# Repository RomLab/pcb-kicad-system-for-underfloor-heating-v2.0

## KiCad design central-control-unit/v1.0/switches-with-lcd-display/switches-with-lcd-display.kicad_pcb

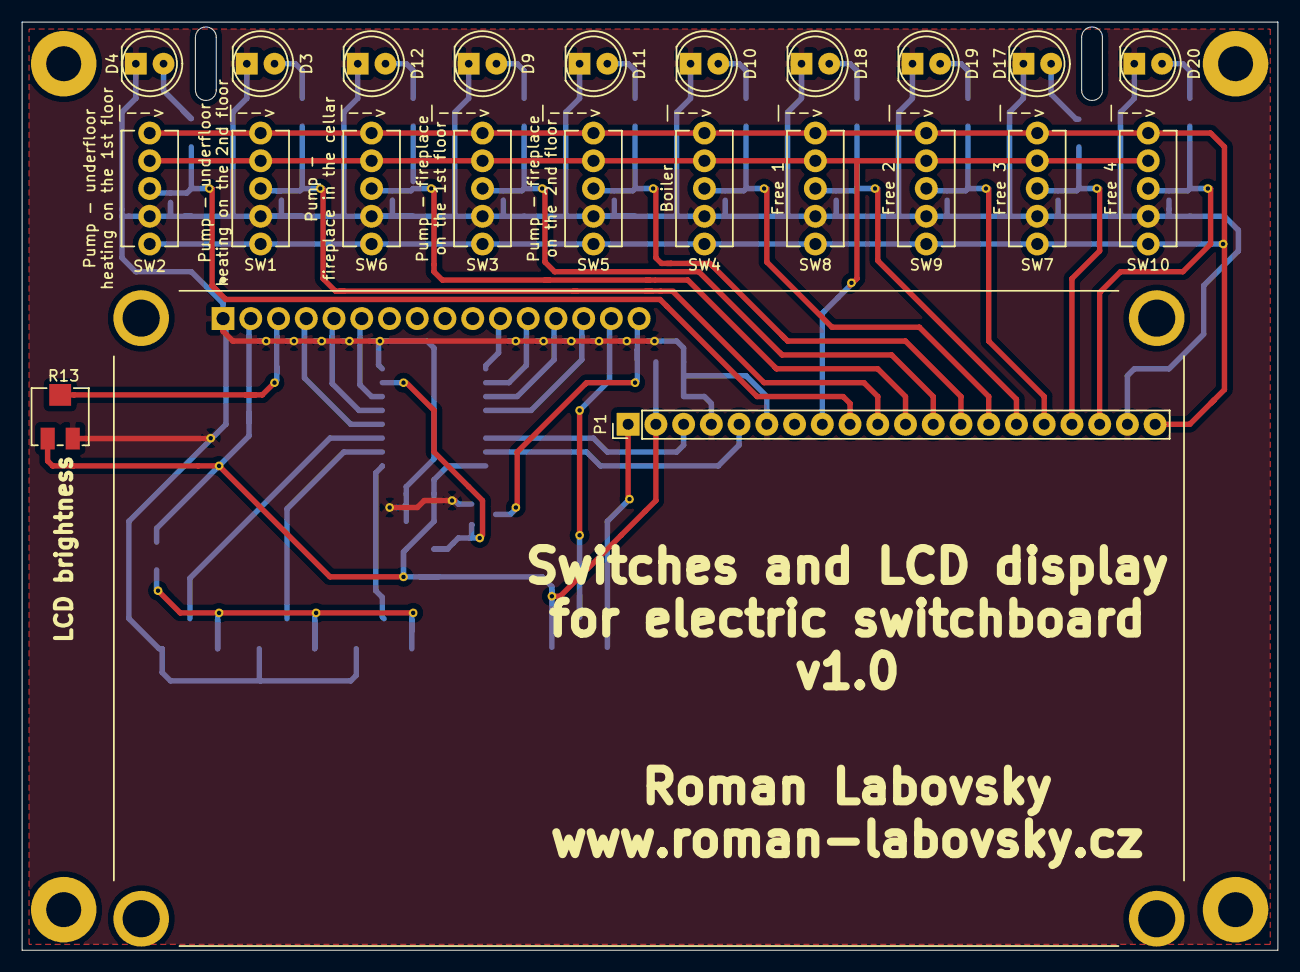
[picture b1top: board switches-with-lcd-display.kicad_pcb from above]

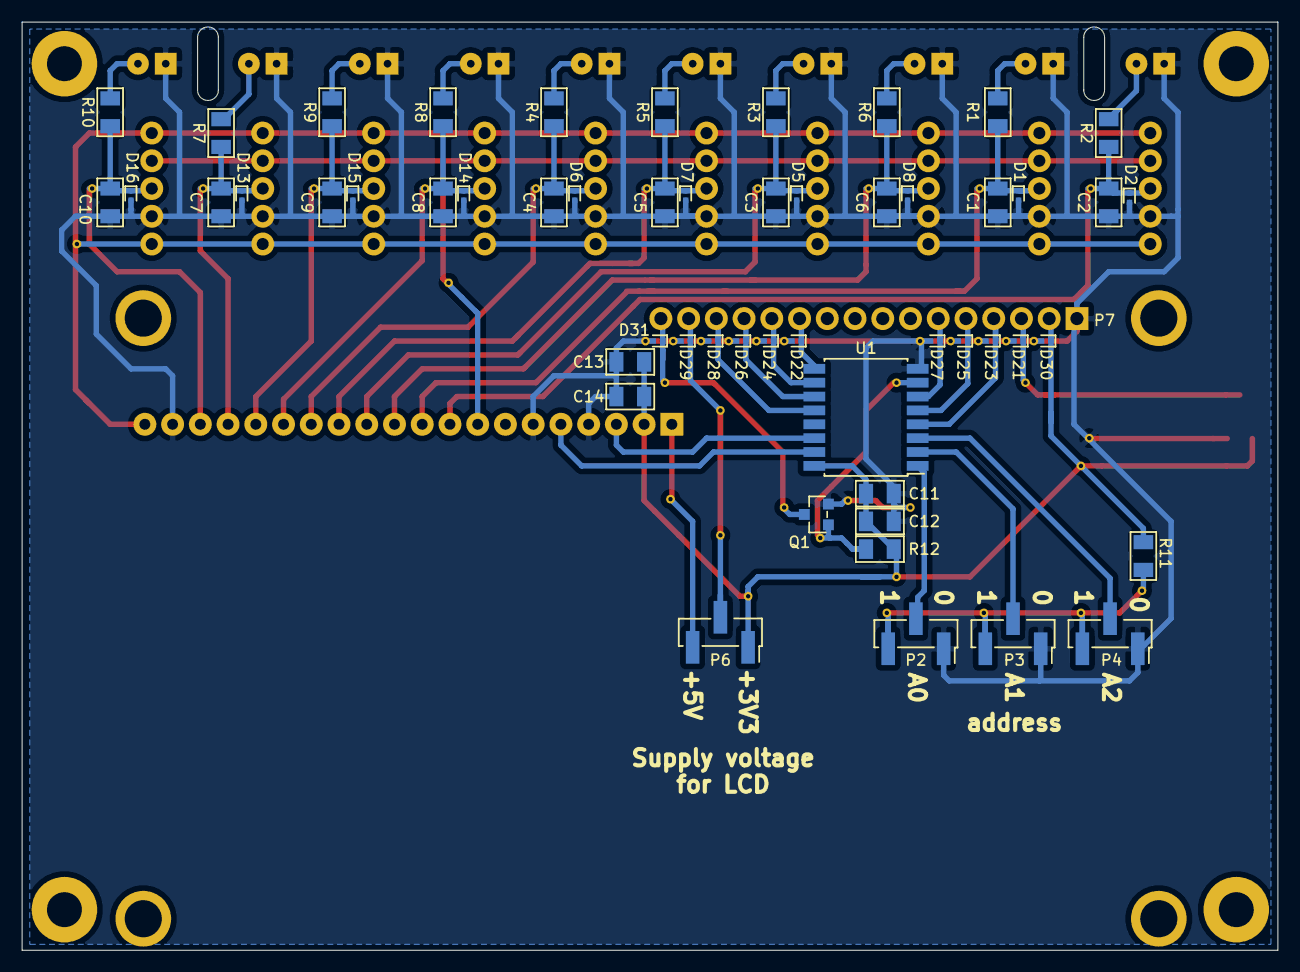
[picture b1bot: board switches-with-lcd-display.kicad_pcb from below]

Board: 2 copper layers, 115.0 x 85.0 mm, 76 parts (53 on the bottom side), 42 nets.

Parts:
C1, C2, C3, C4, C5, C6, C7, C8, C9, C10, C11, C14: 100nF; c_1206
C12, C13: 1uF; c_1206
D1, D2, D5, D6, D7, D8, D13, D14, D15, D16, D21, D22, D23, D24, D25, D26, D27, D28, D29, D30, D31: ESD9R3.3ST5G; sod_923
D3, D4, D9, D10, D11, D12, D17, D18, D19, D20: LL-504PGC1E-G5-2B; led_d5mm_2.54mm
P1: 1x20_pin_header; 1x20_pinheader_2.54mm_vertical
P2, P3, P4, P6: 1x3_pin_header; 1x3_pinheader_2.54mm_vertical
P7: 1x16_pin_header; lcd_module_2004a_20x4
Q1: PMV213SN,215; sot_23
R1, R2, R3, R4, R5, R6, R7, R8, R9, R10: 30R; r_1206
R11, R12: 10k; r_1206
R13: 10k–20k; trimmer_ts53yj
SW1, SW2, SW3, SW4, SW5, SW6, SW7, SW8, SW9, SW10: SMTS-102-2C2T
U1: PCF8574T; so_16

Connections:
/CS: D27.1, P7.6, U1.6
/DB4: D22.1, P7.11, U1.9
/DB5: D24.1, P7.12, U1.10
/DB6: D26.1, P7.13, U1.11
/DB7: D28.1, P7.14, U1.12
/I2C_SCL: P1.3, U1.14
/I2C_SDA: P1.5, U1.15
/LED_A: D29.1, P6.2, P7.15
/LED_K: D31.1, P7.16, Q1.3
/P3_LED_K: Q1.1, R12.2, U1.7
/PCF8574T_A0: P2.2, U1.1
/PCF8574T_A1: P3.2, U1.2
/PCF8574T_A2: P4.2, U1.3
/RS: D23.1, P7.4, U1.4
/RW: D25.1, P7.5, U1.5
/SWITCH_BOILER_3V3: C4.1, D6.1, P1.14, R4.1, SW4.3
/SWITCH_FREE1_3V3: C8.1, D14.1, P1.15, R8.1, SW8.3
/SWITCH_FREE2_3V3: C9.1, D15.1, P1.16, R9.1, SW9.3
/SWITCH_FREE3_3V3: C7.1, D13.1, P1.17, R7.1, SW7.3
/SWITCH_FREE4_3V3: C10.1, D16.1, P1.18, R10.1, SW10.3
/SWITCH_PUMP_FIREPLACE_CELLAR_3V3: C6.1, D8.1, P1.11, R6.1, SW6.3
/SWITCH_PUMP_FIREPLACE_FIRST_FLOOR_3V3: C3.1, D5.1, P1.12, R3.1, SW3.3
/SWITCH_PUMP_FIREPLACE_SECOND_FLOOR_3V3: C5.1, D7.1, P1.13, R5.1, SW5.3
/SWITCH_PUMP_UNDERFLOOR_HEATING_FIRST_FOOR_3V3: C2.1, D2.1, P1.9, R2.1, SW2.3
/SWITCH_PUMP_UNDERFLOOR_HEATING_SECOND_FOOR_3V3: C1.1, D1.1, P1.10, R1.1, SW1.3
/VO: D21.1, P7.3, R13.2
Earth_Protective: P1.20, SW1.1, SW1.5, SW2.1, SW2.5, SW3.1, SW3.5, SW4.1, SW4.5, SW5.1, SW5.5, SW6.1, SW6.5, SW7.1, SW7.5, SW8.1, SW8.5, SW9.1, SW9.5, SW10.1, SW10.5
GND_A: C1.2, C2.2, C3.2, C4.2, C5.2, C6.2, C7.2, C8.2, C9.2, C10.2, C11.1, C12.1, C13.1, C14.1, D1.2, D2.2, D3.1, D4.1, D5.2, D6.2, D7.2, D8.2, D9.1, D10.1, D11.1, D12.1, D13.2, D14.2, D15.2, D16.2, D17.1, D18.1, D19.1, D20.1, D21.2, D22.2, D23.2, D24.2, D25.2, D26.2, D27.2, D28.2, D29.2, D30.2, D31.2, P1.4, P1.6, P1.19, P2.1, P3.1, P4.1, P7.1, Q1.2, R13.1, SW1.4, SW2.4, SW3.4, SW4.4, SW5.4, SW6.4, SW7.4, SW8.4, SW9.4, SW10.4, U1.8
unnamed: D3.2, R1.2
unnamed: D4.2, R2.2
unnamed: D9.2, R3.2
unnamed: D10.2, R4.2
unnamed: D11.2, R5.2
unnamed: D12.2, R6.2
unnamed: D17.2, R7.2
unnamed: D18.2, R8.2
unnamed: D19.2, R9.2
unnamed: D20.2, R10.2
unnamed: P2.3, P3.3, P4.3, R11.2
OTHER_+3V3_A: C11.2, C12.2, C13.2, C14.2, D30.1, P1.2, P6.1, P7.2, R11.1, R12.1, R13.3, U1.16
OTHER_+3V3_B: P1.8, SW1.2, SW2.2, SW3.2, SW4.2, SW5.2, SW6.2, SW7.2, SW8.2, SW9.2, SW10.2
OTHER_+5V: P1.1, P6.3

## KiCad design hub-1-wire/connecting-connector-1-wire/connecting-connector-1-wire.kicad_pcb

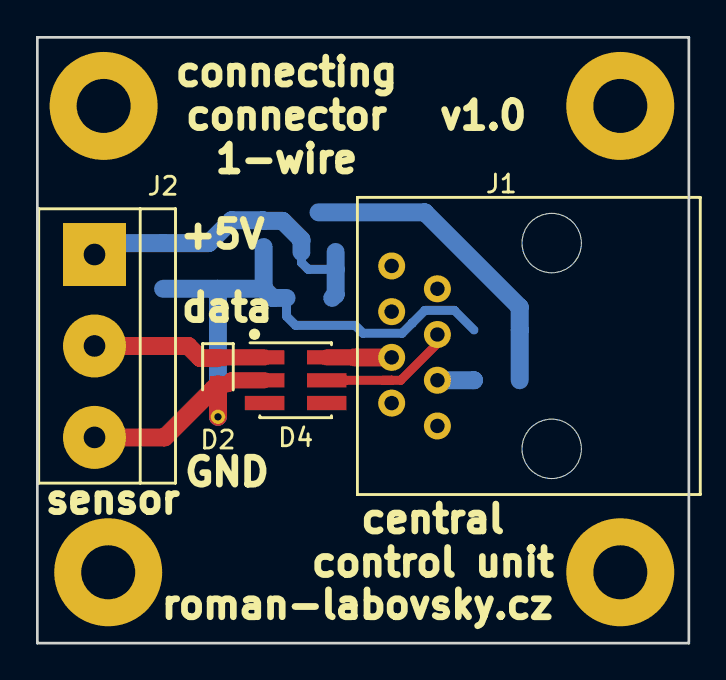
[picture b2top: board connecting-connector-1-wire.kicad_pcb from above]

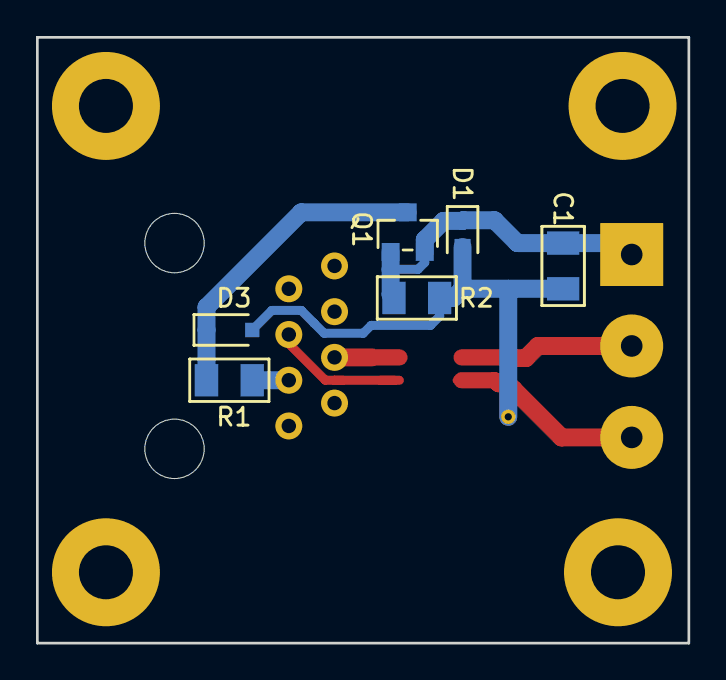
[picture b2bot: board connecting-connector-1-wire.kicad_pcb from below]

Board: 2 copper layers, 36.2 x 33.7 mm, 10 parts (6 on the bottom side), 7 nets.

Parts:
C1: 10uF; c_1206
D1, D2: UCLAMP0501H.TCT; sod_523
D3: ESD3B5V0WS; sod_323
D4: DS9503; tsoc_6
J1: 54601-908WPLF; rj45_54601-908WPLF
J2: Screw_Terminal_01x03; EBBA-03-C-SS-BU
Q1: YJL3415A; sot_23
R1: 10R/0.5W; r_1206
R2: 100k; r_1206

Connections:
/1WIRE_5V: J1.3, R1.1
/1WIRE_5V_OUT: C1.1, D1.1, J2.1, Q1.1, Q1.2, R2.2
/data: D4.6, J1.4
GND: C1.2, D1.2, D2.2, D3.2, D4.2, J2.3, R2.1
unnamed: D2.1, D4.1, J2.2
unnamed: D3.1, Q1.3, R1.2
unnamed: D4.5, J1.5

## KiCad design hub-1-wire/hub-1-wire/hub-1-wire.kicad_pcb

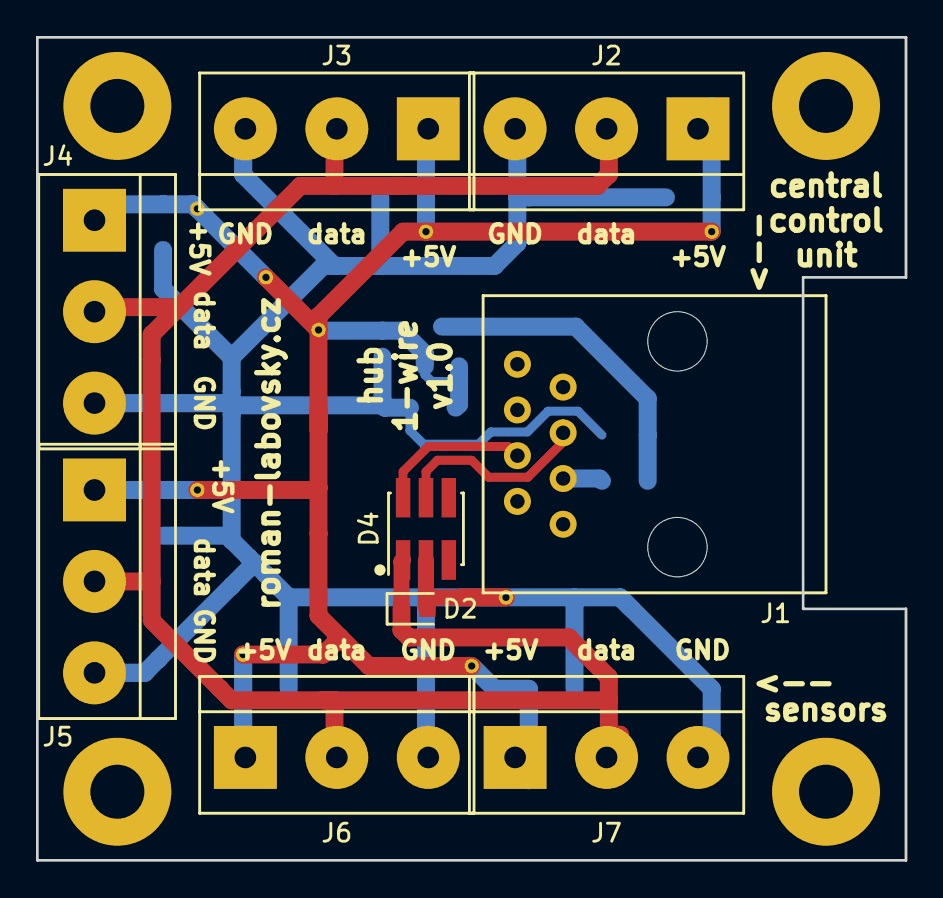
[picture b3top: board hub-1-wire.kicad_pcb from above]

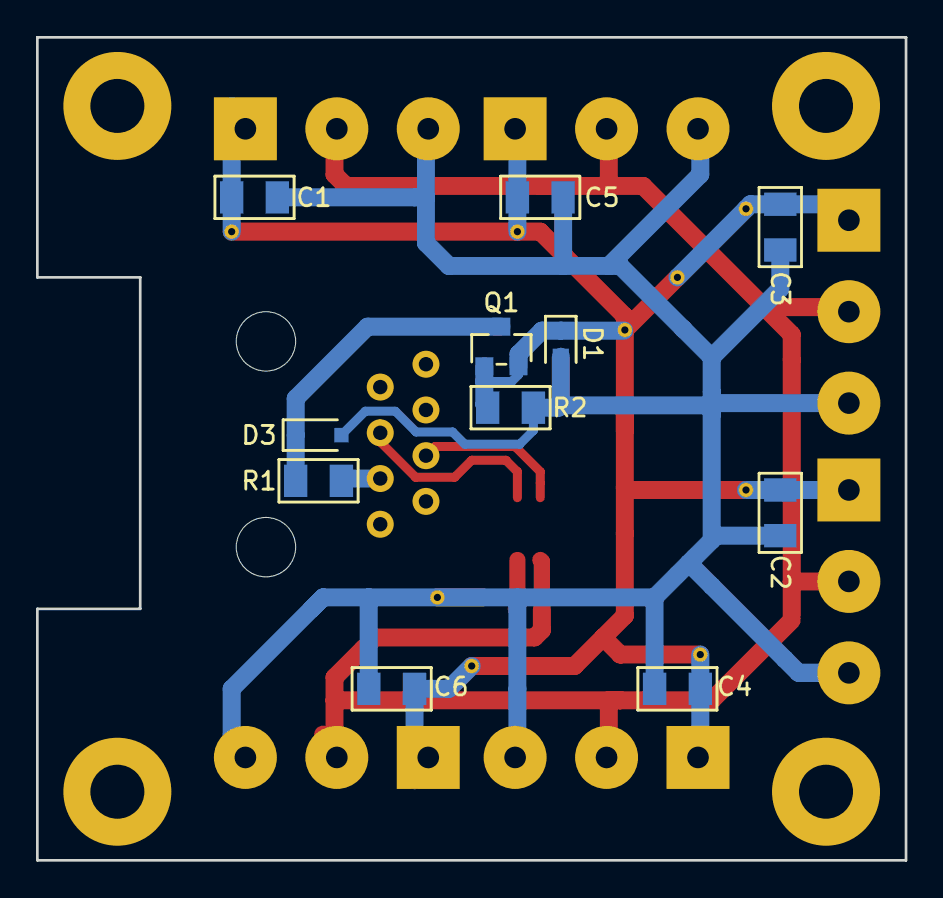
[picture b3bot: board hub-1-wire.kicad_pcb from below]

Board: 2 copper layers, 48.3 x 45.7 mm, 20 parts (11 on the bottom side), 7 nets.

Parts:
C1, C2, C3, C4, C5, C6: 1uF; c_1206
D1, D2: UCLAMP0501H.TCT; sod_523
D3: ESD3B5V0WS; sod_323
D4: DS9503; tsoc_6
J1: RJ45; rj45_54601-908WPLF
J2, J3, J4, J5, J6, J7: Screw_Terminal_01x03; EBBA-03-C-SS-BU
Q1: YJL3415A; sot_23
R1: 10R/0.5W; r_1206
R2: 100k; r_1206

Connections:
/1WIRE_5V: J1.3, R1.2
/1WIRE_5V_OUT: C1.1, C2.1, C3.1, C4.1, C5.1, C6.1, D1.1, J2.1, J3.1, J4.1, J5.1, J6.1, J7.1, Q1.1, Q1.2, R2.1
/data: D4.6, J1.4
GND: C1.2, C2.2, C3.2, C4.2, C5.2, C6.2, D1.2, D2.2, D3.2, D4.2, J2.3, J3.3, J4.3, J5.3, J6.3, J7.3, R2.2
unnamed: D2.1, D4.1, J2.2, J3.2, J4.2, J5.2, J6.2, J7.2
unnamed: D3.1, Q1.3, R1.1
unnamed: D4.5, J1.5

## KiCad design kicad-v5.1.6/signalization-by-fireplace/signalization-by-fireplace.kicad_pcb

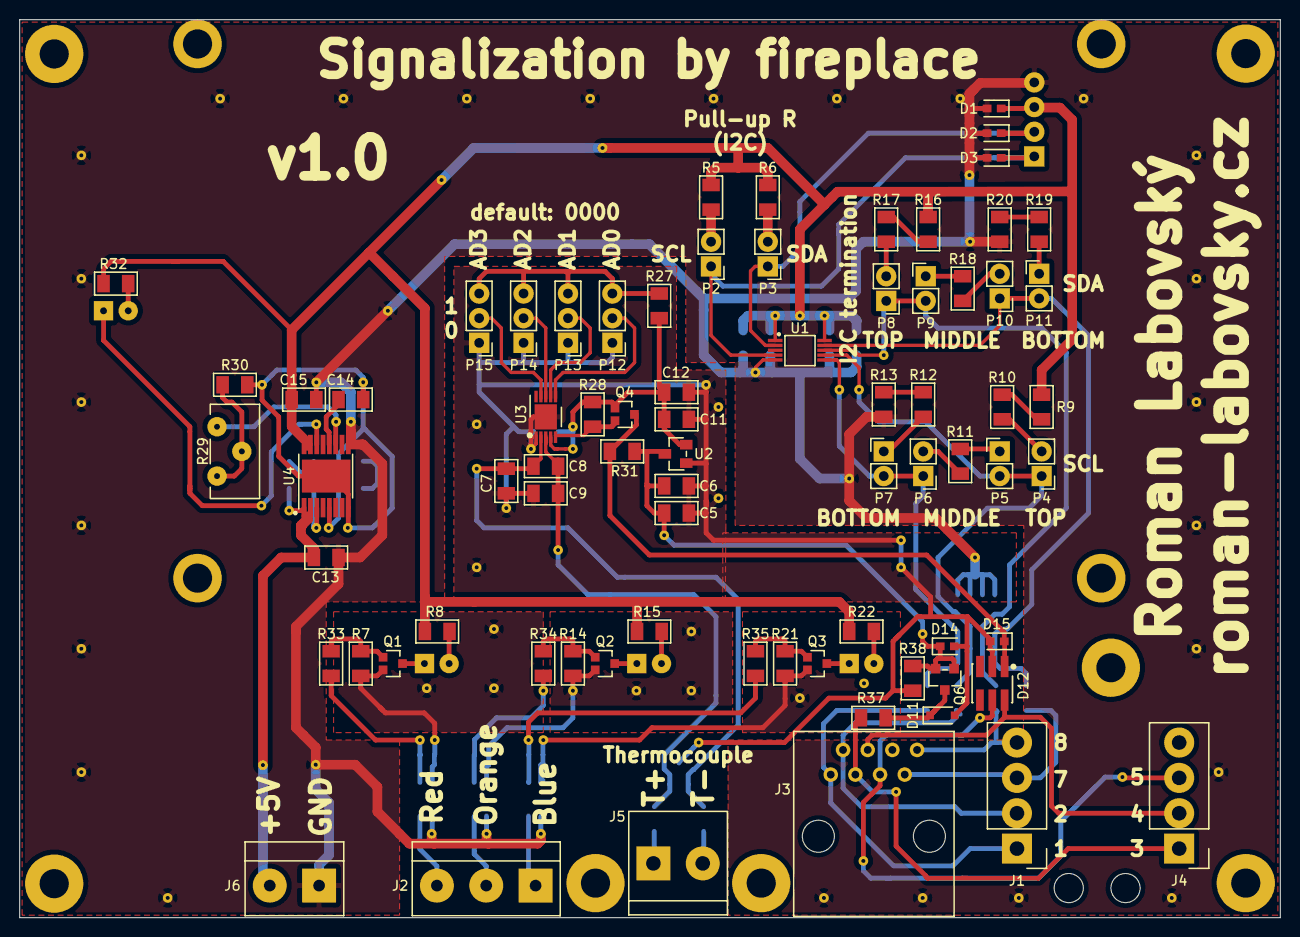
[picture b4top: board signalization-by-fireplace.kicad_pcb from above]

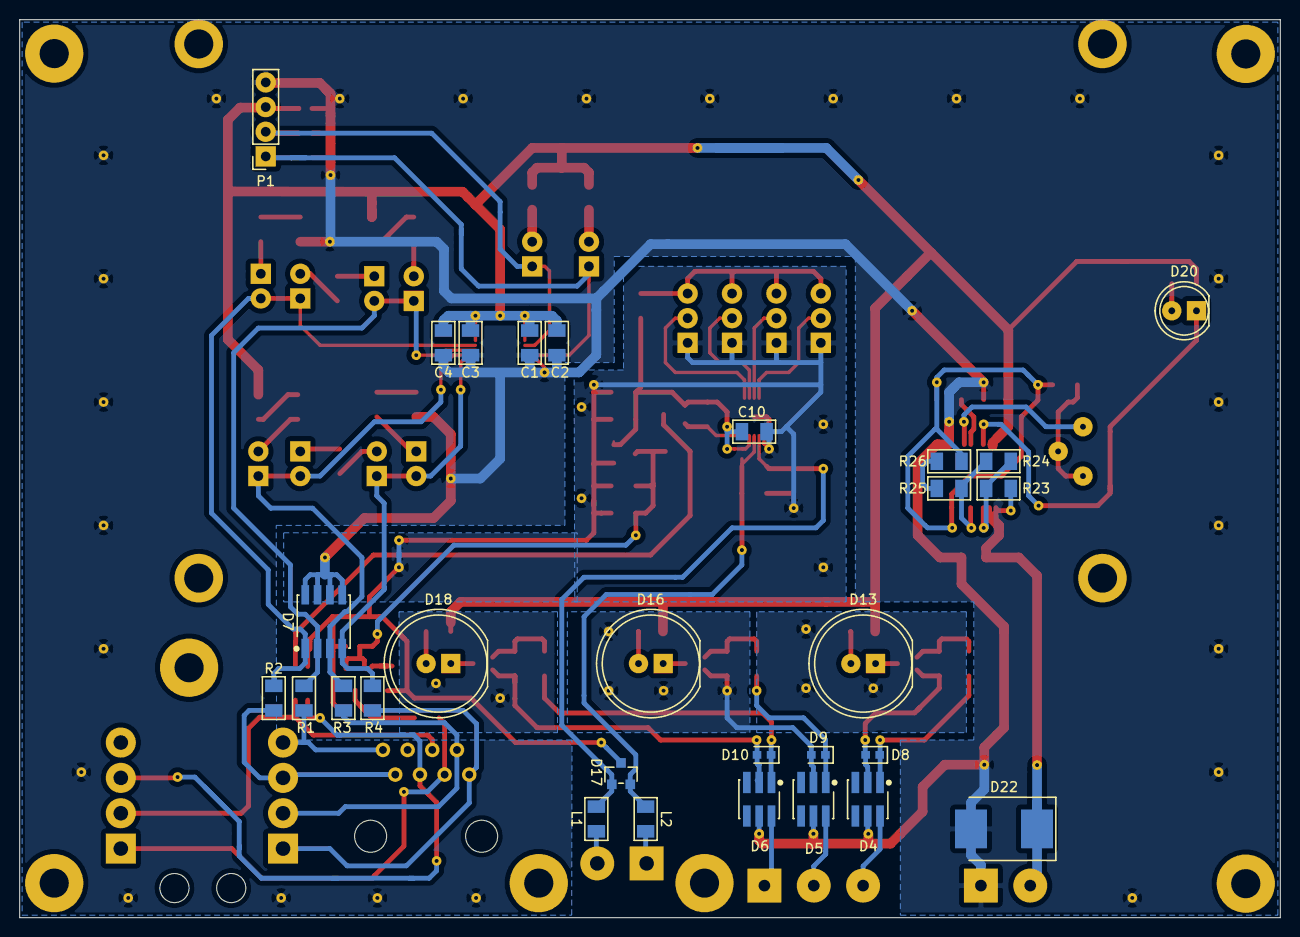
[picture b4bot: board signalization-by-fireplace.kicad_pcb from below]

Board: 2 copper layers, 129.8 x 92.5 mm, 115 parts (29 on the bottom side), 72 nets.

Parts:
 ~: pad_3x5mm
 ~#2,  ~#3,  ~#4: pad_3x5mm
 ~#5,  ~#6,  ~#7,  ~#8,  ~#9,  ~#10,  ~#11: pad_3x6mm
C1, C4, C5, C12, C13, C15: 1uF; c_1206
C2, C3, C6, C10, C11: 100nF; c_1206
C7, C9: NC; c_1206
C8: 10nF; c_1206
C14: 1,2n; c_1206
D1, D2, D3, D8, D9, D10, D14, D15: UCLAMP0501H.TCT; sod_523
D4, D5, D6, D12: DS9503_us; tsoc_6
D7: SMDA05CDR2G; soic_8_3.9mmx4.9mm
D11: ESD3B5V0WS; sod_323
D13: OSB5SAA6A1A; led_d10mm_2.54mm
D16: OSO5PAA6A1A; led_d10mm_2.54mm
D17: ESD16VHYFHT116; sot_23
D18: OSR5PAA6A1A; led_d10mm_2.54mm
D20: LL-503VC1E-4C; led_d5mm_2.54mm
D22: SMCJ5.0CA-13-F; smc
J1, J4: 2x1x4_idc_lsa; 1x4_idc_lsa_connector_general
J2: DG301-5.0-3P12; DG301-5.0-03P-12-00A(H)
J3: 54601-908WPLF; rj45_54601-908WPLF
J5: DG390-5.0-02P-12-00A(H)
J6: DG301-5.0-02P-12-00A(H)
L1, L2: 470R/1A; ferrite_bead_1206
P1: 1x4_pin_socket; 1x4_pinsocket_2.54mm_vertical_2.5x8.4mm
P2, P3, P4, P5, P6, P7, P8, P9, P10, P11: 1x2_pin_header; 1x2_pinheader_2.54mm_vertical
P12, P13, P14, P15: 1x3_pin_header; 1x3_pinheader_2.54mm_vertical
Q1, Q2, Q3, Q4: BSS138P; sot_323
Q6: YJL3415A; sot_23
R1, R2, R3, R4, R37: 10R/0.5W; r_1206
R5, R6, R27, R28, R31: 4k7; r_1206
R7, R14, R21: 10k; r_1206
R8, R15: 130R; r_1206
R9, R13, R16, R20: 210R; r_1206
R10, R12, R17, R19: 390R; r_1206
R11, R18: 100R/120R; r_1206
R22: 100R; r_1206
R23, R38: 100k; r_1206
R24: 3K16; r_1206
R25: 30k; r_1206
R26: 200R; r_1206
R29: 200k; trimmer_t93yb
R30: 5k36; r_1206
R32: 470R; r_1206
R33, R34, R35: 1k; r_1206
U1: PCA9615; tssop10
U2: AP2210N-3.3TRG1; sot_23_3
U3: MAX31850K; tdfn_10_ep
U4: TPS26600; htssop_16_6.6mm×5.1mm

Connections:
+3V3: C10.1, C11.1, C12.1, Q4.1, R27.1, R28.1, U2.2, U3.4
+5V: C1.1, C2.1, C3.1, C4.1, C15.1, D1.1, P1.3, R5.1, R6.1, R8.1, R9.1, R15.1, R16.1, R22.1, R32.1, U1.1, U1.10, U4.15, U4.16
/1WIRE_5V: J3.3, J4.1, R37.1
/1WIRE_5V_OUT: C5.1, C6.1, D14.1, Q6.1, Q6.2, R31.1, R38.1, U2.3
/1WIRE_DATA: D12.6, J3.4, J4.2
/1WIRE_DATA_OUT: D12.1, D15.1, Q4.3, R31.2
/1WIRE_GND: D12.5, J3.5, J4.3
/AD0: P12.2, U3.6
/AD1: P13.2, U3.7
/AD2: P14.2, U3.8
/AD3: P15.2, U3.9
/BLUE: D6.1, D10.1, R35.2
/DQ: Q4.2, R28.2, U3.5
/DSCL_N: D7.4, P6.1, P7.2, R4.2, U1.6
/DSCL_N_CON: J1.1, J3.1, R4.1
/DSCL_P: D7.3, P4.1, P5.2, R3.2, U1.7
/DSCL_P_CON: J1.2, J3.2, R3.1
/DSDA_N: D7.1, P10.1, P11.2, R2.2, U1.9
/DSDA_N_CON: J1.3, J3.7, R2.1
/DSDA_P: D7.2, P8.1, P9.2, R1.2, U1.8
/DSDA_P_CON: J1.4, J3.8, R1.1
/ORANGE: D5.1, D9.1, R34.2
/RED: D4.1, D8.1, R33.2
/SCL: D3.1, P1.1, P2.1, U1.4
/SDA: D2.1, P1.2, P3.1, U1.2
GND: C1.2, C2.2, C3.2, C4.2, C13.2, C15.2, D1.2, D2.2, D3.2, D4.5, D5.5, D6.5, D7.5, D7.6, D7.7, D7.8, D22.2, J6.1, P1.4, R13.2, R20.2, U1.5, U4.9
GND1: D4.2, D8.2, Q1.2, R7.2
GND2: D5.2, D9.2, Q2.2, R14.2
GND3: D6.2, D10.2, Q3.2, R21.2
GND4: C5.2, C6.2, C7.1, C9.2, C10.2, C11.2, C12.2, D11.2, D12.2, D14.2, D15.2, D17.3, P12.1, P13.1, P14.1, P15.1, R38.2, U2.1, U3.1, U3.11
unnamed: C7.2, C8.1, D17.1, L1.2, U3.2
unnamed: C8.2, C9.1, D17.2, L2.2, U3.3
unnamed: C13.1, D22.1, J6.2, R23.1, U4.1, U4.2
unnamed: C14.1, U4.12
unnamed: C14.2, R26.2, R30.1, U4.8, U4.17
unnamed: D4.6, J2.3
unnamed: D5.6, J2.2
unnamed: D6.6, J2.1
unnamed: D11.1, Q6.3, R37.2
unnamed: D13.1, Q1.3
unnamed: D13.2, R8.2
unnamed: D16.1, Q2.3
unnamed: D16.2, R15.2
unnamed: D18.1, Q3.3
unnamed: D18.2, R22.2
unnamed: D20.1, U4.14
unnamed: D20.2, R32.2
unnamed: J5.1, L2.1
unnamed: J5.2, L1.1
unnamed: P2.2, R5.2
unnamed: P3.2, R6.2
unnamed: P4.2, R10.2
unnamed: P5.1, R11.1
unnamed: P6.2, R11.2
unnamed: P7.1, R12.1
unnamed: P8.2, R17.2
unnamed: P9.1, R18.1
unnamed: P10.2, R18.2
unnamed: P11.1, R19.1
unnamed: P12.3, P13.3, P14.3, P15.3, R27.2
unnamed: Q1.1, R7.1, R33.1
unnamed: Q2.1, R14.1, R34.1
unnamed: Q3.1, R21.1, R35.1
unnamed: R9.2, R10.1
unnamed: R12.2, R13.1
unnamed: R16.2, R17.1
unnamed: R19.2, R20.1
unnamed: R23.2, R24.1, U4.3
unnamed: R24.2, R25.1, U4.5
unnamed: R25.2, R26.1
unnamed: R29.1, R29.2, R30.2
unnamed: R29.3, U4.11

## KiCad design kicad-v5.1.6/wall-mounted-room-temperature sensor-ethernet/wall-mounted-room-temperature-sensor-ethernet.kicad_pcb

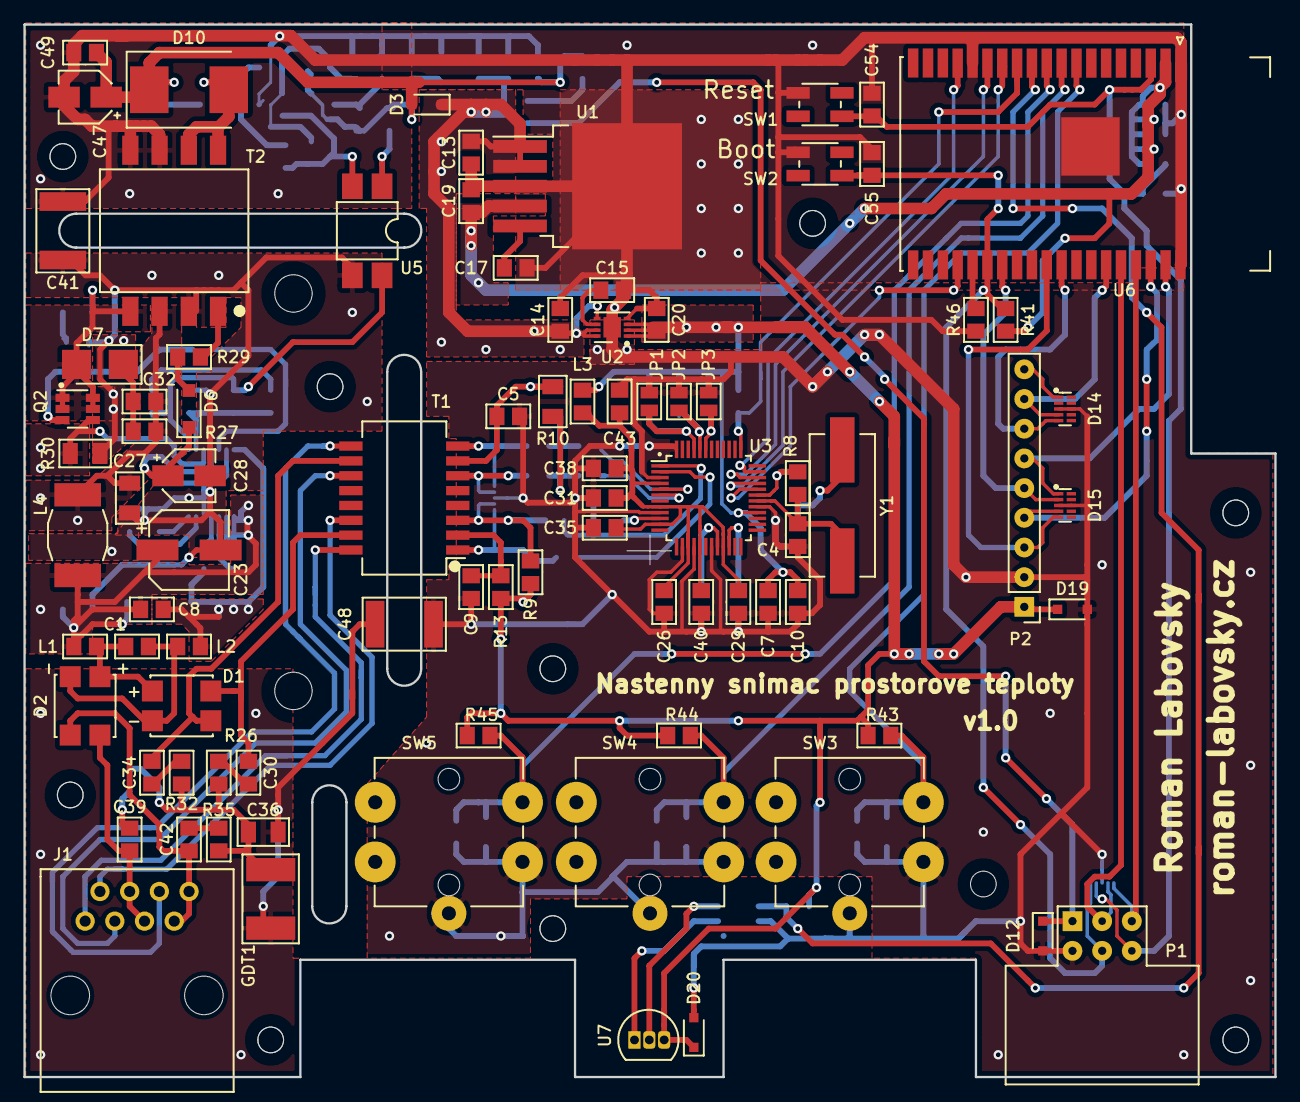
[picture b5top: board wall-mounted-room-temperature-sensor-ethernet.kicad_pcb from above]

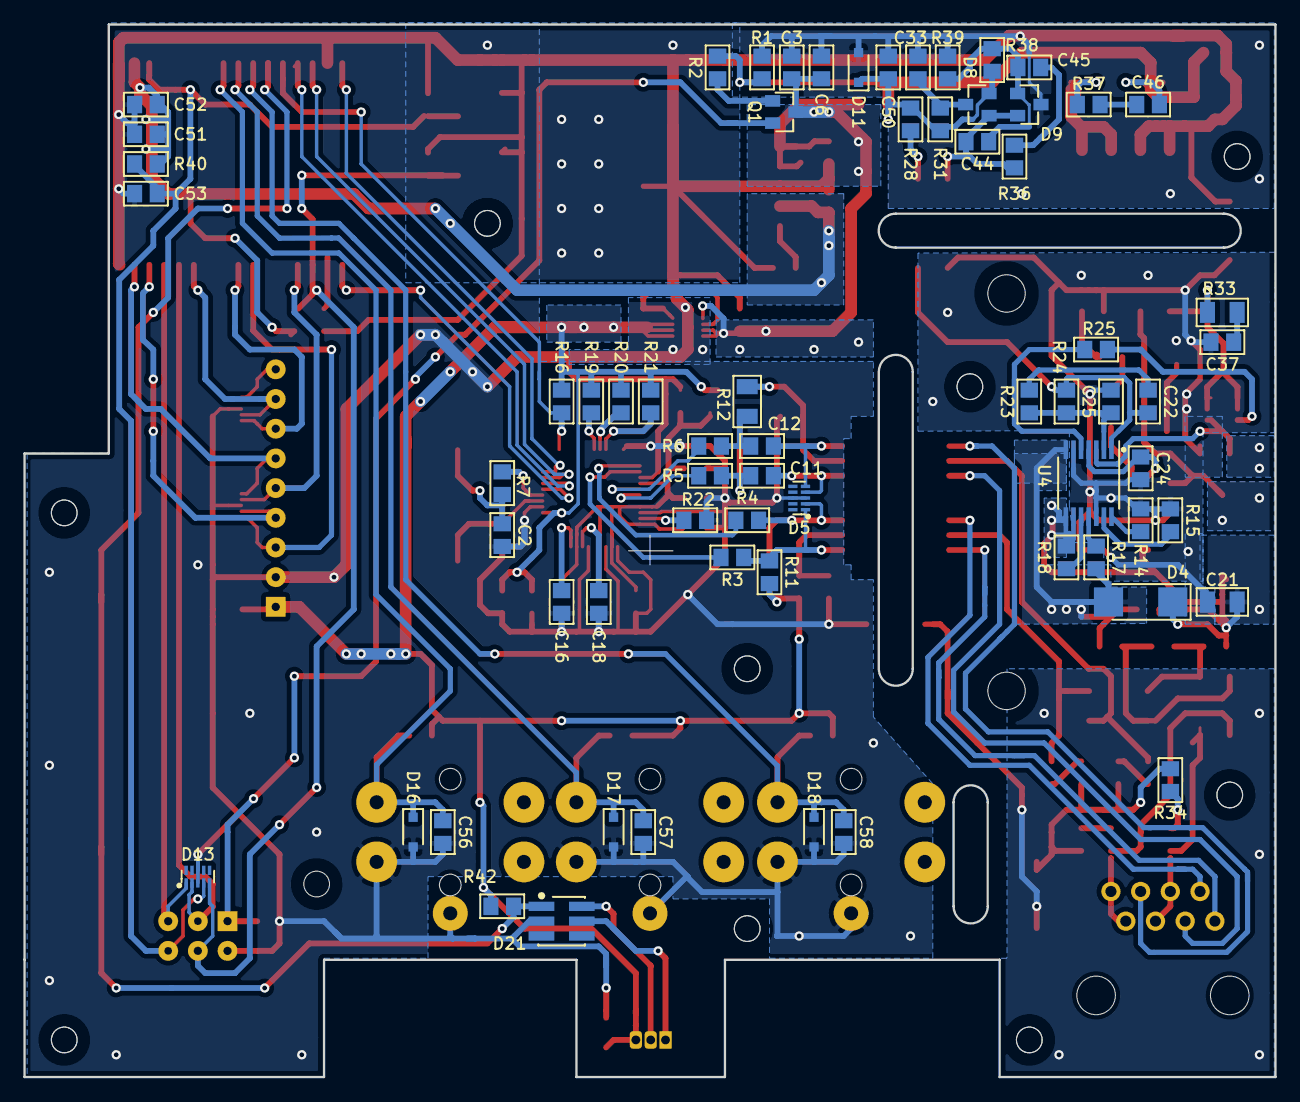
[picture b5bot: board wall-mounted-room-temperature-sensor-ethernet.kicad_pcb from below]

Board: 2 copper layers, 107.0 x 90.0 mm, 153 parts (66 on the bottom side), 97 nets.

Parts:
C1: 1nF/100V; c_0805
C2, C4: 18pF; c_0805
C3: 22uF/25V; c_0805
C5, C15, C17: 10nF/16V; c_0805
C6, C33: 1uF/16V; c_0805
C7, C43: 10uF; c_0805
C8: 100nF/100V; c_0805
C9: 22nF/16V; c_0805
C10, C26, C29, C31, C35, C38, C40, C52, C54, C55, C56, C57, C58: 100nF; c_0805
C11, C12: 6,8nF/16V; c_0805
C13, C14: 2.2uF/16V; c_0805
C16: 10nF; c_0805
C18: 4,7uF; c_0805
C19, C20: 10uF/16V; c_0805
C21, C27: 1uF/100V; c_1206
C22: 22nF/50V; c_0805
C23: 22uF/63V; elec_c_6,3x7,7
C24: 0,22uF/25V; c_0805
C25: 100nF/50V; c_0805
C28: 10uF/16V; elec_c_4x5,8
C30, C32, C34, C39, C42: 10nF/100V; c_0805
C36: 1nF/2kV; c_1206
C37: 330pF/200V; c_0805
C41: 2200pF/2kV; c_1812_gal_space
C44: 100pF/50V; c_0805
C45: 8,2nF/50V; c_0805
C46: 680pF/25V; c_0805
C47: 47uF/6,3V; elec_c_4x5,8
C48: 4700pF/2kV; c_1812_gal_space
C49, C50: 47uF/10V; c_0805
C51: 22uF; c_0805
C53: 1uF; c_0805
D1, D2: HD01-T; mini_dip
D3: BAT60B; sod_323
D4: SMAJ58A; do_214ac
D5, D13, D14, D15: PHDMI2AB4Z; dfn_2510a_10
D6: BAV16W-7; sod_123
D7: MURA120; sma
D8: BAV99LT1G; sot_23_3
D9: TLV431ACDBZR; sot_23_3
D10: MBRS540T3; smc_do_214ab
D11, D12, D16, D17, D18, D19, D20: SD05.TCT; sod_323
D21: DS9503_us; tsoc_6
GDT1: 2051-09-SM-RPLF
J1: rj45; rj45_54601-908WPLF
JP1, JP2, JP3: solder_jumper_2_open; solder_jumper_2_open_rect_1x1,5mm
L1, L2: MMZ2012R150A; r_0805
L3: BLM21PG121SN1D; r_0805
L4: 4,7uH/1,5A; DO1608C-472ML
P1: 2x3_pins_header; 2x3_pin_header_MLW06A
P2: 1x9_pin_header; 1x9_v_pin_header
Q1: DMG2307L; sot_23_3
Q2: FDC2512; super_sot_6
R1, R2: 100k; r_0805
R3, R4, R5, R6: 33; r_0805
R7: 0R; r_0805
R8: 1M; r_0805
R9, R11, R25, R29: 49,9R; r_0805
R10, R12: 82R; r_1206
R13: 10R; r_0805
R14: 59k; r_0805
R15: 80,6k; r_0805
R16, R19, R20, R21, R31, R40, R41, R43, R44, R45, R46: 10k; r_0805
R17: 1,27k; r_0805
R18: 24k9; r_0805
R22: 12,4k; r_0805
R23: 499R; r_0805
R24: 2k; r_0805
R26, R32, R34, R35: 75R; r_0805
R27: 49,9k; r_0805
R28: 1k; r_0805
R30: 0,56R; r_1206
R33: 82R/0,5W; r_1206
R36: 19,1k; r_0805
R37: 20R; r_0805
R38: 41,2k; r_0805
R39: 13,3k; r_0805
R42: 4,7k; r_0805
SW1, SW2: TVAF18BB
SW3, SW4, SW5: B3F-4150
T1: SM13126PEL
T2: POE70P-50L
U1: TPS79633KTTR; to_263_5
U2: TPS7A8033DRBR; son_8
U3: W5500; lqfp_48
U4: TPS23753A; tssop14
U5: FOD817AS; dip_4
U6: ESP32-WROVER-IE
U7: DS18B20; to_92_in_line
Y1: 25MHz; ABLS2-25.000MHZ-D4YF-T

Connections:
+5V: C3.1, C6.1, C13.1, C14.1, D3.1, Q1.3, U1.1, U1.2, U2.5, U2.7, U2.8
/1wire_data: D21.1, R42.2, U6.11
/DISPLAY_CLK: D14.5, P2.7, U6.30
/DISPLAY_CS: D15.5, P2.3, U6.29
/DISPLAY_DCRS: D15.2, P2.5, U6.26
/DISPLAY_LED: D14.4, P2.8, U6.33
/DISPLAY_MOSI: D15.1, P2.6, U6.37
/DISPLAY_RST: D15.4, P2.4, U6.36
/EN: C53.1, C54.1, D13.4, P1.6, R40.2, SW1.1, U6.3
/IO0: C55.1, D13.5, P1.4, R41.2, SW2.1, U6.25
/NOT_CONNECTED: D14.1, P2.9
/P45: C39.1, D2.4, J1.4, J1.5
/P78: C42.1, D2.3, J1.7, J1.8
/RX+: R5.1, U3.6
/RX-: R6.1, U3.5
/RXCM: C34.1, D1.3, T1.10
/RXD: D13.2, P1.3, U6.34
/TX+: R3.1, U3.2
/TX-: R4.1, U3.1
/TXCM: C30.1, D1.4, T1.15
/TXD: D13.1, P1.5, U6.35
/W5500_CLK: U3.33, U6.13
/W5500_CS: U3.32, U6.23
/W5500_MISO: U3.34, U6.14
/W5500_MOSI: U3.35, U6.16
/W5500_RST: R16.2, U3.37, U6.12
/button1: C56.1, D16.1, R43.2, SW3.3, U6.8
/button2: C57.1, D17.1, R44.2, SW4.3, U6.9
/button3: C58.1, D18.1, R45.2, SW5.3, U6.10
AVDD: C26.1, C29.1, C31.1, C35.1, C38.1, C40.1, C43.1, L3.2, U3.4, U3.8, U3.11, U3.15, U3.17, U3.21
GND: C2.2, C3.2, C4.2, C5.2, C6.2, C7.2, C9.2, C10.2, C13.2, C14.2, C15.2, C16.2, C17.2, C18.2, C19.2, C20.2, C26.2, C29.2, C31.2, C33.2, C35.2, C38.2, C40.2, C41.2, C43.2, C47.2, C48.2, C49.1, C50.2, C51.2, C52.2, C53.2, C54.2, C55.2, C56.2, C57.2, C58.2, D5.3, D5.8, D9.3, D11.2, D12.2, D13.3, D13.8, D14.3, D14.8, D15.3, D15.8, D16.2, D17.2, D18.2, D19.2, D20.2, D21.2, JP1.2, JP2.2, JP3.2, P1.2, P2.2, R1.2, R22.2, R39.2, R46.2, SW1.4, SW2.4, SW3.1, SW3.5, SW4.1, SW4.5, SW5.1, SW5.5, T2.5, T2.6, U1.3, U2.4, U2.9, U3.3, U3.9, U3.14, U3.16, U3.19, U3.29, U3.48, U6.1, U6.15, U6.38, U6.39
GNDPWR: C36.2, C48.1, GDT1.2
GNDREF: C21.2, C23.2, C24.2, C25.2, C27.2, C28.2, C37.2, C41.1, R14.2, R15.2, R30.2, T2.2, U4.6, U4.12, U5.3
unnamed: C1.1, D1.1, D2.1, L1.1
unnamed: C1.2, D1.2, D2.2, L2.1
unnamed: C2.1, R7.2, Y1.1
unnamed: C4.1, R8.2, U3.30, Y1.2
unnamed: C5.1, R10.2, R12.2, T1.7
unnamed: C8.2, D4.2, L2.2, R17.2, U4.7
unnamed: C9.1, R13.2, T1.2
unnamed: C11.1, R5.2, R10.1
unnamed: C11.2, D5.4, T1.6
unnamed: C12.1, R6.2, R12.1
unnamed: C12.2, D5.5, T1.8
unnamed: C15.1, U2.6
unnamed: C16.1, U3.22
unnamed: C17.1, U1.5
unnamed: C18.1, U3.20
unnamed: C8.1, C21.1, C23.1, D4.1, L1.2, L4.1, R18.1, U4.8, U4.9
unnamed: C22.1, R23.2
unnamed: C22.2, R24.2, U4.1, U5.4
unnamed: C24.1, C28.1, D6.1, U4.4
unnamed: C25.1, R23.1, R24.1, U4.2
unnamed: C27.1, C32.1, L4.2, R27.1, T2.3
unnamed: C30.2, R26.1
unnamed: C32.2, D7.1, R27.2
unnamed: C33.1, D8.3, R31.2
unnamed: C34.2, R32.1
unnamed: C36.1, GDT1.1, R26.2, R32.2, R34.2, R35.2
unnamed: C37.1, R33.2
unnamed: C39.2, R34.1
unnamed: C42.2, R35.1
unnamed: C44.1, D8.1, D9.2, R36.1, U5.2
unnamed: C44.2, C45.2, D9.1, R38.2, R39.1
unnamed: C45.1, R36.2
unnamed: C46.1, R37.2
unnamed: D5.1, R3.2, R11.2, T1.1
unnamed: D5.2, R4.2, R9.2, T1.3
unnamed: D6.2, R29.1
unnamed: D7.2, Q2.1, Q2.2, Q2.5, Q2.6, R33.1, T2.4
unnamed: D10.2, R37.1, T2.7, T2.8
unnamed: D21.5, U7.1
unnamed: D21.6, U7.2
unnamed: J1.1, T1.16
unnamed: J1.2, T1.14
unnamed: J1.3, T1.11
unnamed: J1.6, T1.9
unnamed: JP3.1, R19.2, U3.43
unnamed: JP2.1, R20.2, U3.44
unnamed: JP1.1, R21.2, U3.45
unnamed: Q1.1, R2.2
unnamed: Q2.3, R25.2
unnamed: Q2.4, R30.1, U4.3
unnamed: R7.1, R8.1, U3.31
unnamed: R14.1, U4.14
unnamed: R15.1, U4.13
unnamed: R17.1, U4.11
unnamed: R18.2, U4.10
unnamed: R22.1, U3.10
unnamed: R25.1, U4.5
unnamed: R28.2, U5.1
unnamed: R29.2, T2.1
unnamed: R46.1, U6.24
OTHER_+3,3V: C7.1, C10.1, C20.1, D19.1, D20.1, L3.1, P2.1, R9.1, R11.1, R13.1, R16.1, R19.1, R20.1, R21.1, R42.1, R43.1, R44.1, R45.1, U2.1, U2.2, U2.3, U3.28, U7.3
POE_+5V: C46.2, C47.1, C49.2, C50.1, D3.2, D8.2, D10.1, D11.1, R1.1, R2.1, R28.1, R31.1, R38.1
SYS_+3,3V: C19.1, C51.1, C52.1, R40.1, R41.1, U1.4, U6.2
USB_+5V: D12.1, P1.1, Q1.2
